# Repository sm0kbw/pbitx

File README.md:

# pbitx

Pbitx is a replacement for the arduino in Ubitx v6, it´s based on the Raspberry Pi Pico micro controller.

It contains software written in C, the code is a rework of the ubitxv6-master branch some files are replaced/added.
The name is a combination of Pico and Ubitx resulting in Pbitx.

Changed or replaced files is for instance the file handling CW, it's replaced with my own state machine. I also use my own CI-V interpreter.
Beside thiose files I have made a lot of changes in the code, and I like to think that I have simplified some code.
I use a set of fonts from http://www.rinkydinkelectronics.com/r_fonts.php/ thank you for those files.

I've added a S-meter and a panorama-mode, both dependent on a extended ND6T AGC ciricuit. The panaroma mode means that a broader frequency
span is sweept and presented as s spectrum on the display, this is how it was done in ancient times, of course the reciever isn't usable
in this mode. Pbitx has three CW modes, straight key, plain respective iambic bugg mode. CAT is now a subset of the CI-V interrface. 
For now it's just a couple of commands implemented such as setting and reading the frequency, changing mode and switch between RX and TX mode.
The structure of the interpreter makes it very easy to add more of the CI-V commands.

Hardware design files can be found in the PCB folder and the subfolder AGC.
There are two Kicad designs the first on is the adapter that replace the Arduino with a RPI Pico controller. The second one is an
AGC detector it is used by some functions, S-Meter and a panoram scope, The detector is based on ND6T's design with some extra components added.

This is, of course, a work in progress and features will be added and bugg fixed.

Bengt - SM0KBW 	2023-Nov-01

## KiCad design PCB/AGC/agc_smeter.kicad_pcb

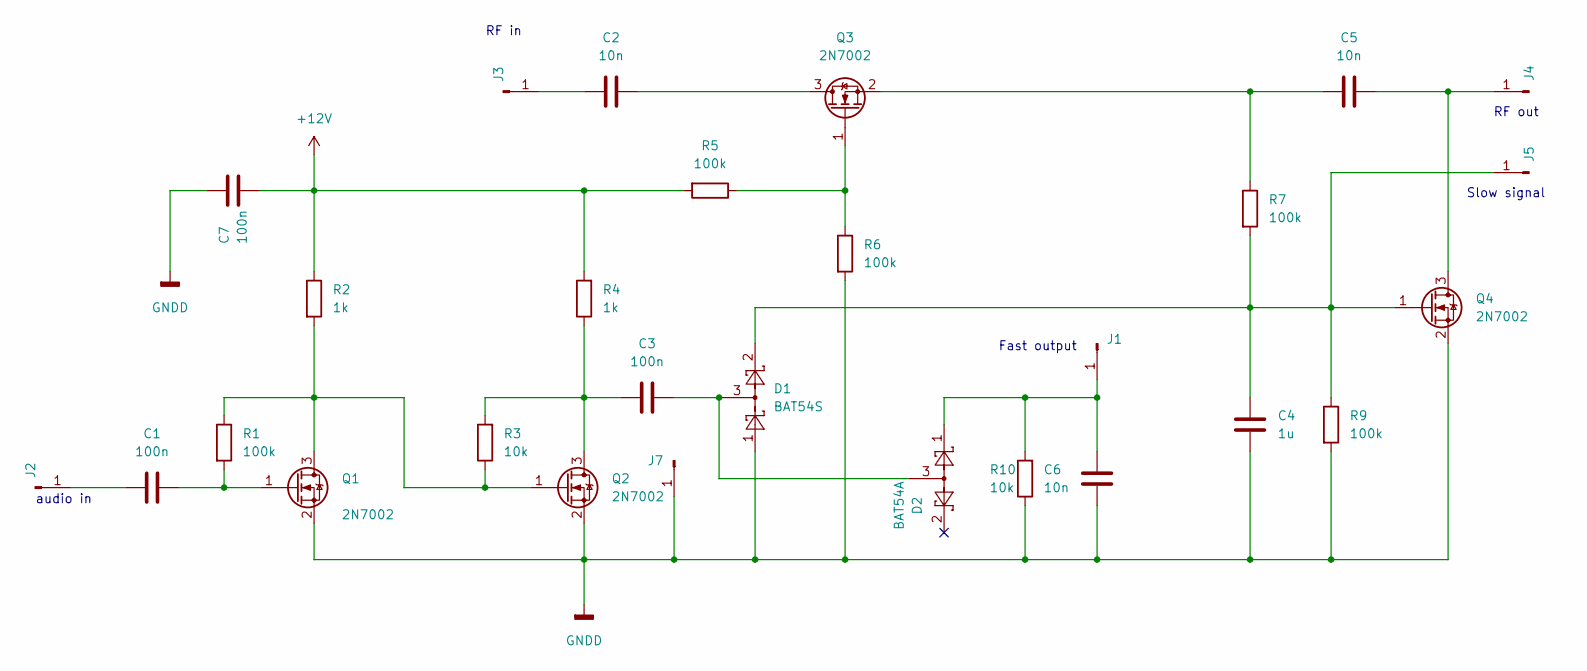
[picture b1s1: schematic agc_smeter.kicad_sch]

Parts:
C1, C3, C7: 100n; C_0603_1608Metric
C2, C5, C6: 10n; C_0603_1608Metric
C4: 1u; C_0805_2012Metric
D1: BAT54S; SOT-23
D2: BAT54A; SOT-23
J1, J2, J3, J4, J5, J7: Conn_01x01_Pin; SolderWire-0.5sqmm_1x01_D0.9mm_OD2.1mm
Q1, Q2, Q3, Q4: 2N7002; SOT-23
R1, R5, R6, R7, R9: 100k; R_0603_1608Metric
R2, R4: 1k; R_0603_1608Metric
R3, R10: 10k; R_0603_1608Metric

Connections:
GNDD: C4.1, C6.1, C7.2, D1.1, J7.1, Q1.2 (S), Q2.2 (S), Q4.2 (S), R6.2, R9.2, R10.1
unnamed: C3.2, D1.3, D2.3
unnamed: C6.2, D2.1, J1.1, R10.2
unnamed: C1.1, J2.1
unnamed: C2.2, J3.1
unnamed: C5.1, J4.1, Q4.3 (D)
unnamed: C4.2, D1.2, J5.1, Q4.1 (G), R7.2, R9.1
unnamed 7: C7.1, R2.1, R4.2, R5.2; also elsewhere on the board
unnamed: Q1.3 (D), Q2.1 (G), R1.1, R2.2, R3.1
unnamed: C1.2, Q1.1 (G), R1.2
unnamed: C3.1, Q2.3 (D), R3.2, R4.1
unnamed: C2.1, Q3.3 (D)
unnamed: Q3.1 (G), R5.1, R6.1
unnamed: C5.2, Q3.2 (S), R7.1

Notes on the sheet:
Fast output
RF in
audio in
Slow signal
RF out

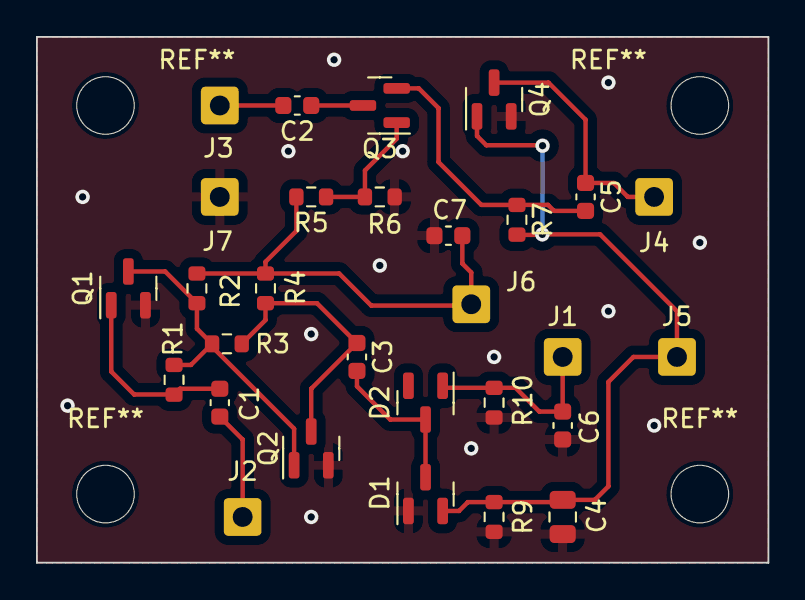
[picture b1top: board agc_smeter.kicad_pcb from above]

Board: 2 copper layers, 40.6 x 29.2 mm, 29 parts (0 on the bottom side), 14 nets.

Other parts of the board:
J6: Conn_01x01_Pin; SolderWire-0.5sqmm_1x01_D0.9mm_OD2.1mm

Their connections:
unnamed 7: J6.1; also elsewhere on the board

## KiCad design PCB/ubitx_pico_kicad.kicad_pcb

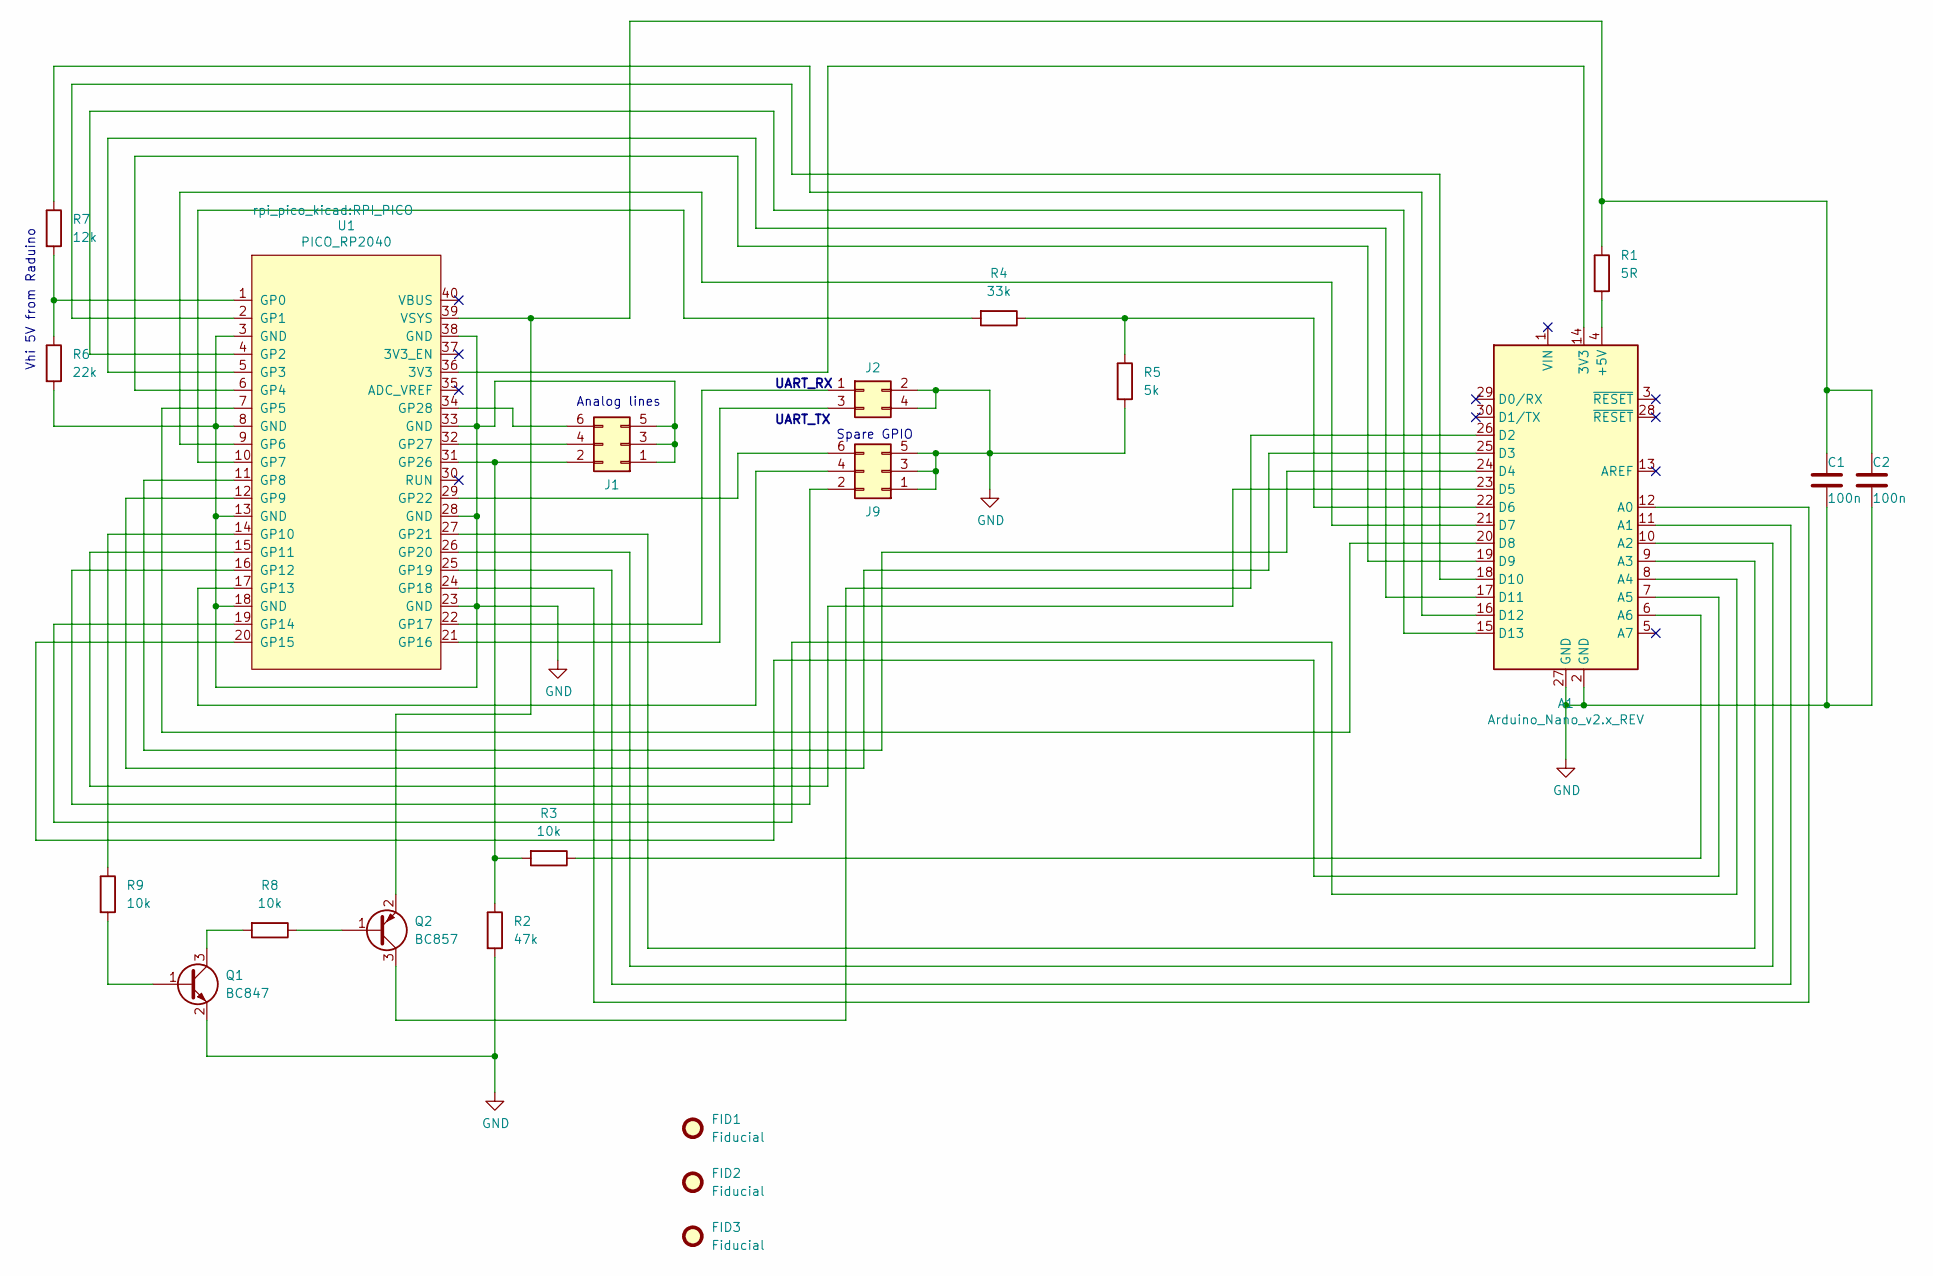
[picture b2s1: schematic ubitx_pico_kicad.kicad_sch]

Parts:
A1: Arduino_Nano_v2.x_REV; Arduino_Nano
C1, C2: 100n; C_0805_2012Metric
FID1, FID2, FID3: Fiducial; Fiducial_0.5mm_Mask1.5mm
J1, J9: Conn_02x03_Odd_Even; PinSocket_2x03_P2.54mm_Vertical
J2: Conn_02x02_Odd_Even; PinSocket_2x02_P2.54mm_Vertical
Q1: BC847; SOT-23
Q2: BC857; SOT-23
R1: 5R; R_0805_2012Metric
R2: 47k; R_0805_2012Metric
R3, R8, R9: 10k; R_0805_2012Metric
R4: 33k; R_0805_2012Metric
R5: 5k; R_0805_2012Metric
R6: 22k; R_0805_2012Metric
R7: 12k; R_0805_2012Metric
U1: PICO_RP2040; RPI_PICO

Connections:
GND: A1.2 (GND), A1.27 (GND), C1.2, C2.2, J1.1, J1.3, J1.5, J2.2, J2.4, J9.1, J9.3, J9.5, Q1.2 (E), R2.2, R5.2, R6.2, U1.3 (GND), U1.8 (GND), U1.13 (GND), U1.18 (GND), U1.23 (GND), U1.28 (GND), U1.33 (GND), U1.38 (GND)
unnamed: A1.14 (3V3), U1.36 (3V3)
unnamed: A1.4 (+5V), R1.2
unnamed: A1.12 (A0), U1.24 (GP18)
unnamed: A1.11 (A1), U1.25 (GP19)
unnamed: A1.10 (A2), U1.26 (GP20)
unnamed: A1.9 (A3), U1.27 (GP21)
unnamed: A1.8 (A4), U1.19 (GP14)
unnamed: A1.7 (A5), U1.20 (GP15)
unnamed: A1.6 (A6), R3.1
unnamed: A1.26 (D2), Q2.3 (C)
unnamed: A1.25 (D3), U1.12 (GP9)
unnamed: A1.24 (D4), U1.11 (GP8)
unnamed: A1.23 (D5), U1.15 (GP11)
unnamed: A1.22 (D6), R4.1, R5.1
unnamed: A1.21 (D7), U1.9 (GP6)
unnamed: A1.20 (D8), U1.7 (GP5)
unnamed: A1.19 (D9), U1.6 (GP4)
unnamed: A1.18 (D10), U1.2 (GP1)
unnamed: A1.17 (D11), U1.5 (GP3)
unnamed: A1.16 (D12), R7.1
unnamed: A1.15 (D13), U1.4 (GP2)
unnamed: J1.2, R2.1, R3.2, U1.31 (GP26)
unnamed: J1.4, U1.32 (GP27)
unnamed: J1.6, U1.34 (GP28)
unnamed: J2.1, U1.22 (GP17)
unnamed: J2.3, U1.21 (GP16)
unnamed: J9.2, U1.16 (GP12)
unnamed: J9.4, U1.17 (GP13)
unnamed: J9.6, U1.29 (GP22)
unnamed: Q1.1 (B), R9.2
unnamed: Q1.3 (C), R8.2
unnamed: Q2.1 (B), R8.1
unnamed: C1.1, C2.1, Q2.2 (E), R1.1, U1.39 (VSYS)
unnamed: R6.1, R7.2, U1.1 (GP0)
unnamed: R4.2, U1.10 (GP7)
unnamed: R9.1, U1.14 (GP10)

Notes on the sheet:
Spare GPIO
UART_RX
Vhi 5V from Raduino
Analog lines
UART_TX

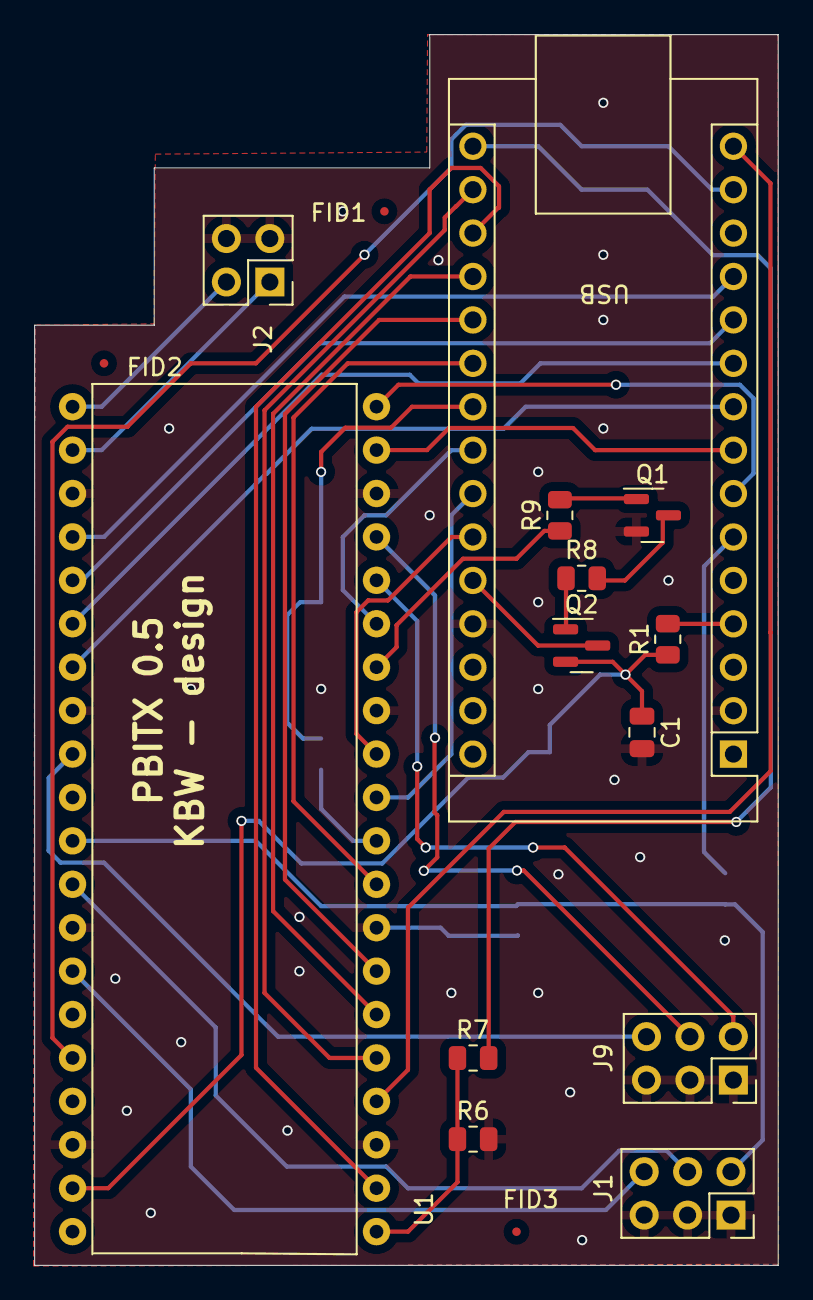
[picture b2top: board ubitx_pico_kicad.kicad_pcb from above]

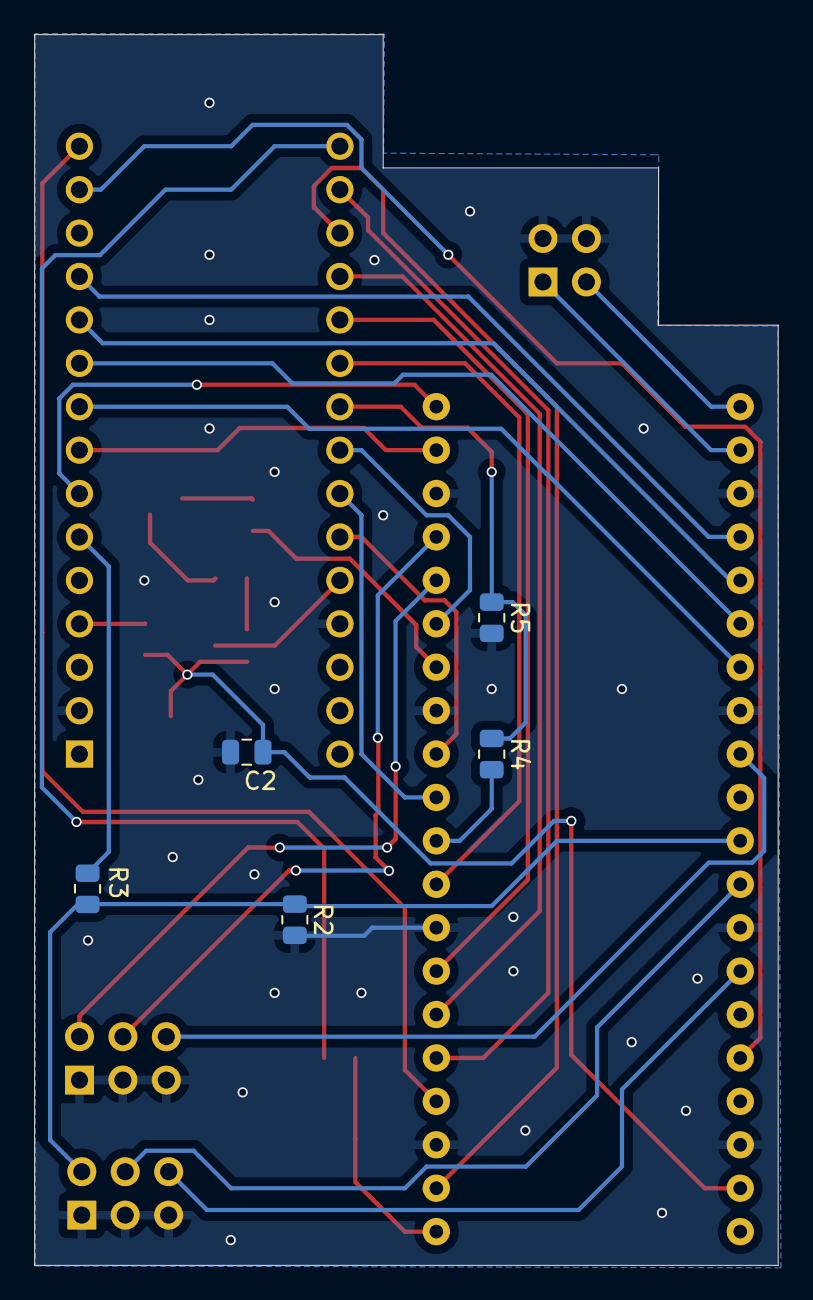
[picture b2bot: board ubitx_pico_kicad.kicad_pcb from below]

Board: 2 copper layers, 43.5 x 72.0 mm, 21 parts (5 on the bottom side), 37 nets.

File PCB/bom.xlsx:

Column1 | Column2 | Column3 | Column4 | Column5 | Column6 | Column7 | Column8
Source: | \\wsl.localhost\Debian\home\boa\pico\project\pbitx\PCB\ubitx_pico_kicad.kicad_s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
Date: | 2023-11-01 14:54:53
Tool: | Eeschema 7.0.7
Generator: | C:\Program Files\KiCad\7.0\bin\scripting\plugins/bom_csv_grouped_by_value.py
Component Count: | 21
Collated Components:
Item | Qty | Reference(s) | Value | LibPart | Footprint | Datasheet | DNP
1 | 1 | A1 | Arduino_Nano_v2.x_REV | ubitx_pico_kicad-rescue:Arduino_Nano_v2.x_REV-arduino_nano_v2.x_rev | Module:Arduino_Nano | https://www.arduino.cc/en/uploads/Main/ArduinoNanoManual23.pdf
2 | 2 | C1, C2 | 100n | Device:C | Capacitor_SMD:C_0805_2012Metric | ~
3 | 3 | FID1, FID2, FID3 | Fiducial | Mechanical:Fiducial | Fiducial:Fiducial_0.5mm_Mask1.5mm | ~
4 | 2 | J1, J9 | Conn_02x03_Odd_Even | Connector_Generic:Conn_02x03_Odd_Even | Connector_PinSocket_2.54mm:PinSocket_2x03_P2.54mm_Vertical | ~
5 | 1 | J2 | Conn_02x02_Odd_Even | Connector_Generic:Conn_02x02_Odd_Even | Connector_PinSocket_2.54mm:PinSocket_2x02_P2.54mm_Vertical | ~
6 | 1 | Q1 | BC847 | Transistor_BJT:BC847 | Package_TO_SOT_SMD:SOT-23 | http://www.infineon.com/dgdl/Infineon-BC847SERIES_BC848SERIE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
7 | 1 | Q2 | BC857 | Transistor_BJT:BC857 | Package_TO_SOT_SMD:SOT-23 | https://www.onsemi.com/pub/Collateral/BC860-D.pdf
8 | 1 | R1 | 5R | Device:R | Resistor_SMD:R_0805_2012Metric | ~
9 | 1 | R2 | 47k | Device:R | Resistor_SMD:R_0805_2012Metric | ~
10 | 3 | R3, R8, R9 | 10k | Device:R | Resistor_SMD:R_0805_2012Metric | ~
11 | 1 | R4 | 33k | Device:R | Resistor_SMD:R_0805_2012Metric | ~
12 | 1 | R5 | 5k | Device:R | Resistor_SMD:R_0805_2012Metric | ~
13 | 1 | R6 | 22k | Device:R | Resistor_SMD:R_0805_2012Metric | ~
14 | 1 | R7 | 12k | Device:R | Resistor_SMD:R_0805_2012Metric | ~
15 | 1 | U1 | PICO_RP2040 | ubitx_pico_kicad-rescue:PICO_RP2040-rpi_pico | rpi_pico_kicad:RPI_PICO

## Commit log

2023-11-01 First upload of the project
2023-11-01 Added Kicad files for the adapter PCB and moved some bin files to build
2023-11-01 Added AGC circuit files and updated README.md
2023-11-01 Added a updated README.md
2023-11-03 some pictures added
2023-11-03 small panorama image added
2023-11-03 adjuted panorama images
